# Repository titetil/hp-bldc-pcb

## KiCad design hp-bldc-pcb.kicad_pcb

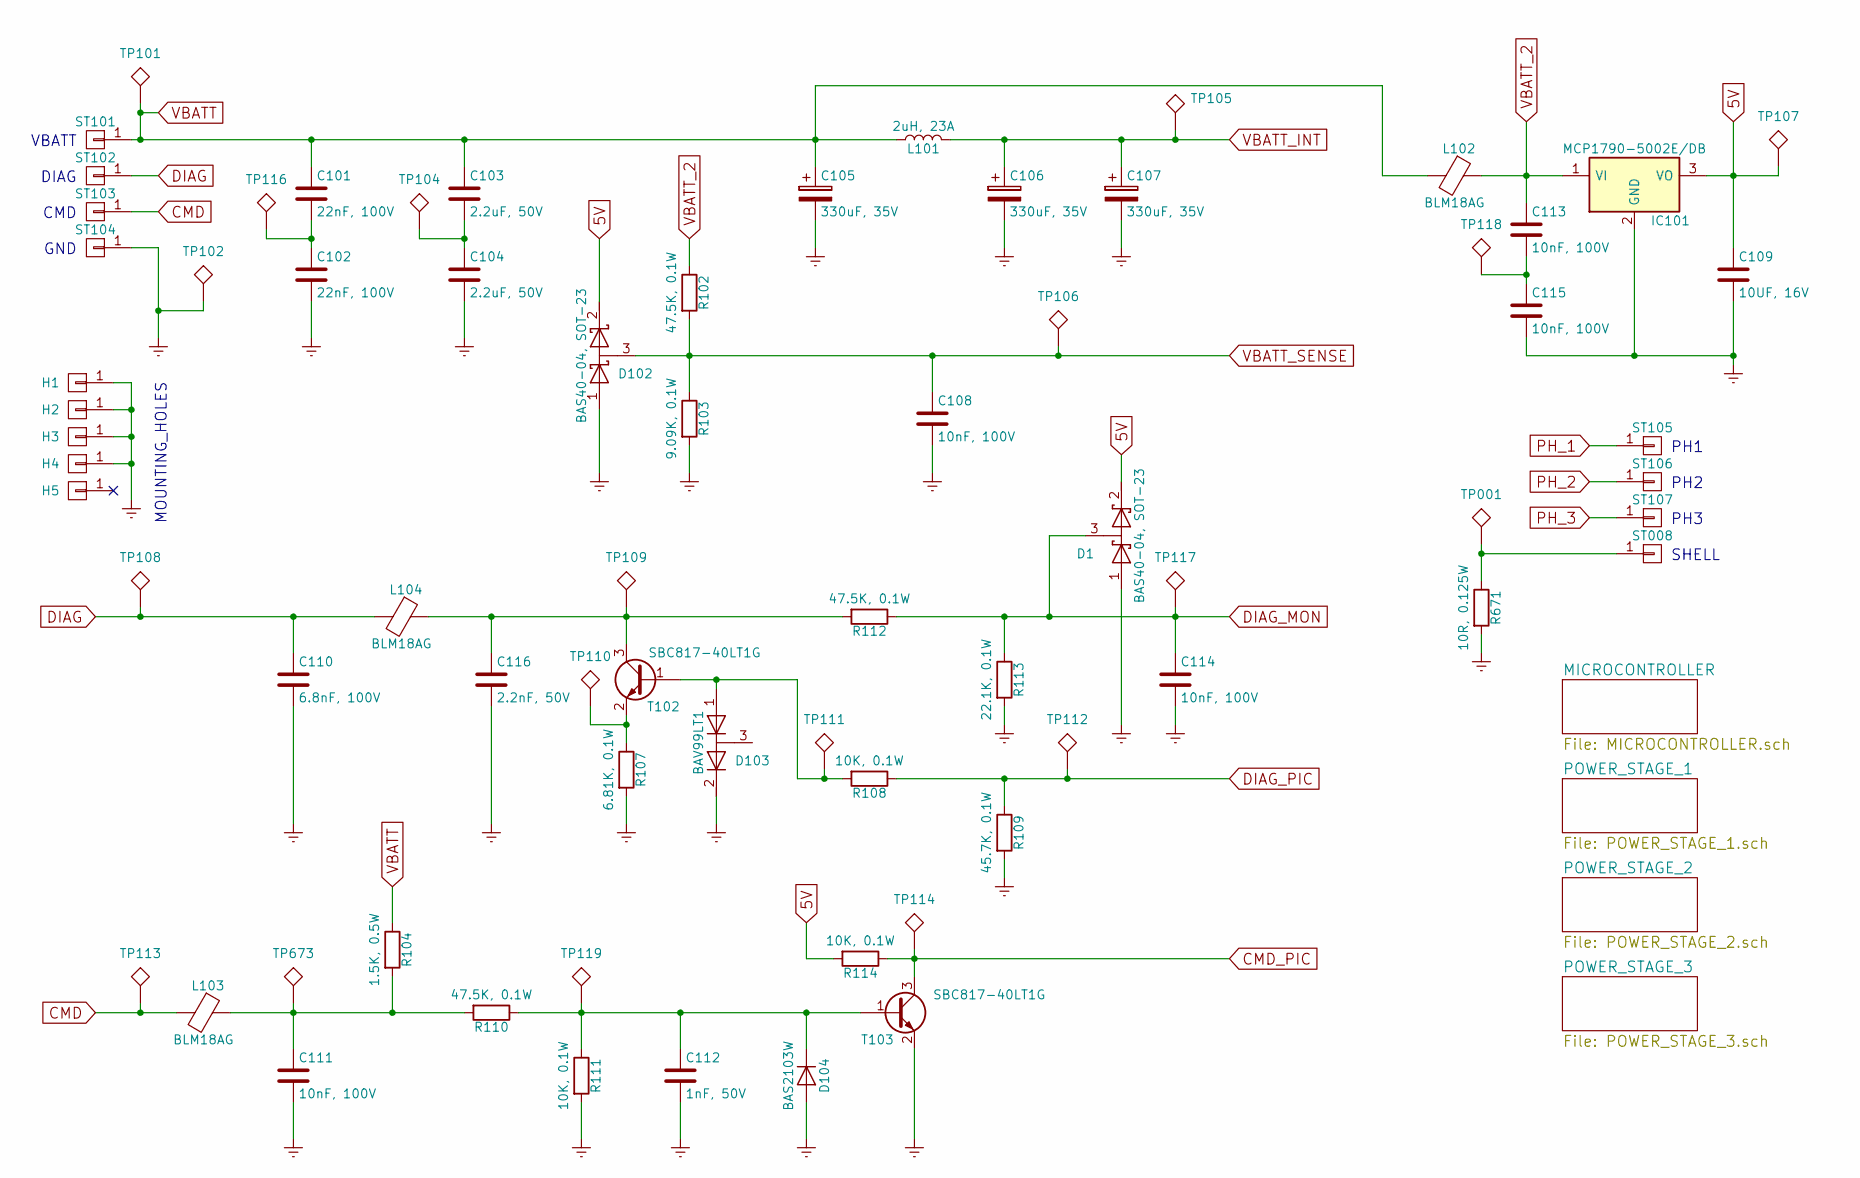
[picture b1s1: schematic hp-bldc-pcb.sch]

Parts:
C101, C102: 22nF, 100V; C_0805
C103, C104: 2.2uF, 50V; C_1206
C105, C106, C107: 330uF, 35V; CP_Elec_10x10
C108, C113, C114, C115: 10nF, 100V; C_0603
C109: 10UF, 16V; C_1206
C110: 6.8nF, 100V; C_0805
C111: 10nF, 100V; C_0805
C112: 1nF, 50V; C_0603
C116: 2.2nF, 50V; C_0603
D1, D102: BAS40-04, SOT-23; SOT-23
D103: BAV99LT1; SOT-23
D104: BAS2103W; D_SOD-323
H1, H2, H3, H4, H5: CONN_01X01; ENCLOSURE_MOUNTING_HOLE
IC101: MCP1790-5002E/DB; SOT-223
L101: 2uH, 23A; L_Wuerth_HCI-1365
L102, L103, L104: BLM18AG; L_0603
R102, R110, R112: 47.5K, 0.1W; R_0603
R103: 9.09K, 0.1W; R_0603
R104: 1.5K, 0.5W; R_1210
R107: 6.81K, 0.1W; R_0603
R108, R111, R114: 10K, 0.1W; R_0603
R109: 45.7K, 0.1W; R_0603
R113: 22.1K, 0.1W; R_0603
R671: 10R, 0.125W; R_0805
ST008, ST101, ST102, ST103, ST104, ST105, ST106, ST107: CONN_01X01; BIG_RECT_PAD
T102, T103: SBC817-40LT1G; SOT-23
TP001, TP101, TP102, TP104, TP105, TP106, TP107, TP108, TP109, TP110, TP111, TP112, TP113, TP114, TP116, TP117, TP118, TP119, TP673: TEST; TEST_POINT_40mil

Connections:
5V: C109.1, D1.2 (K), D102.2 (K), IC101.3 (VO), R114.2, TP107.1; also elsewhere on the board
CMD: L103.2, ST103.1, TP113.1
CMD_PIC: R114.1, T103.3 (C), TP114.1; also elsewhere on the board
DIAG: C110.1, L104.2, ST102.1, TP108.1
DIAG_MON: C114.1, D1.3 (common), R112.1, R113.1, TP117.1; also elsewhere on the board
DIAG_PIC: R108.1, R109.1, TP112.1; also elsewhere on the board
Earth: C102.2, C104.2, C105.2, C106.2, C107.2, C108.2, C109.2, C110.2, C111.2, C112.2, C114.2, C115.2, C116.2, D1.1 (A), D102.1 (A), D103.2 (K), D104.2 (A), H1.1, H2.1, H3.1, H4.1, IC101.2 (GND), IC101.4 (GND), R103.2, R107.2, R109.2, R111.2, R113.2, R671.2, ST104.1, T103.2 (E), TP102.1; also elsewhere on the board
unnamed: C101.2, C102.1, TP116.1
unnamed: C103.2, C104.1, TP104.1
unnamed: C111.1, L103.1, R104.2, R110.2, TP673.1
unnamed: C112.1, D104.1 (K), R110.1, R111.1, T103.1 (B), TP119.1
unnamed: C113.2, C115.1, TP118.1
unnamed: C116.1, L104.1, R112.2, T102.3 (C), TP109.1
unnamed: D103.1 (A), R108.2, T102.1 (B), TP111.1
unnamed: R107.1, T102.2 (E), TP110.1
unnamed: R671.1, ST008.1, TP001.1
PH_1: ST105.1; also elsewhere on the board
PH_2: ST106.1; also elsewhere on the board
PH_3: ST107.1; also elsewhere on the board
VBATT: C101.1, C103.1, C105.1, L101.1, L102.2, R104.1, ST101.1, TP101.1
VBATT_2: C113.1, IC101.1 (VI), L102.1, R102.1
VBATT_INT: C106.1, C107.1, L101.2, TP105.1; also elsewhere on the board
VBATT_SENSE: C108.1, D102.3 (common), R102.2, R103.1, TP106.1; also elsewhere on the board

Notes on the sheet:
PH1
PH2
PH3
SHELL
VBATT
DIAG
CMD
GND
MOUNTING_HOLES

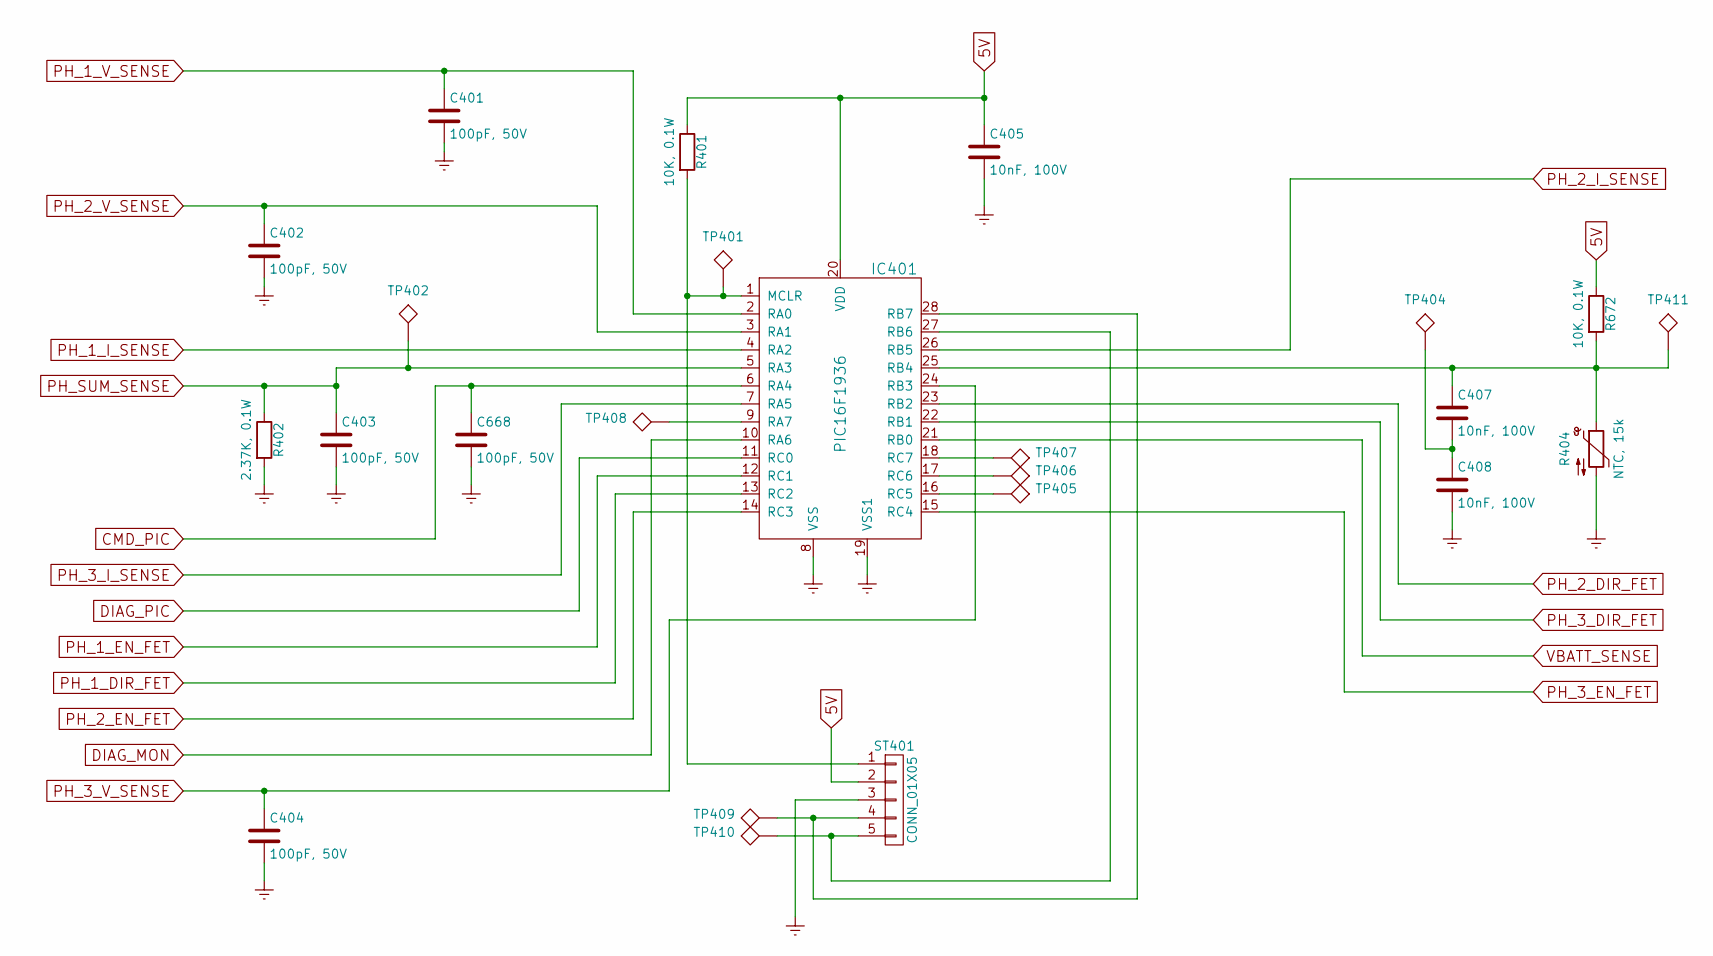
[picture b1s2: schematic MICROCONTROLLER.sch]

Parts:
C401, C402, C403, C404, C668: 100pF, 50V; C_0603
C405, C407, C408: 10nF, 100V; C_0603
IC401: PIC16F1936; SSOP-28_5.3x10.2mm_Pitch0.65mm
R401, R672: 10K, 0.1W; R_0603
R402: 2.37K, 0.1W; R_0603
R404: NTC, 15k; R_0603
ST401: CONN_01X05; Pin_Header_Straight_1x05_Pitch2.54mm_SMD_Pin1Left
TP401, TP402, TP404, TP405, TP406, TP407, TP408, TP409, TP410, TP411: TEST; TEST_POINT_40mil

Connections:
5V: C405.1, IC401.20 (VDD), R401.1, R672.1, ST401.2; also elsewhere on the board
CMD_PIC: C668.1, IC401.6 (RA4); also elsewhere on the board
DIAG_MON: IC401.10 (RA6); also elsewhere on the board
DIAG_PIC: IC401.11 (RC0); also elsewhere on the board
Earth: C401.2, C402.2, C403.2, C404.2, C405.2, C408.2, C668.2, IC401.8 (VSS), IC401.19 (VSS1), R402.2, R404.2, ST401.3; also elsewhere on the board
unnamed: C407.1, IC401.25 (RB4), R404.1, R672.2, TP411.1
unnamed: C407.2, C408.1, TP404.1
unnamed: IC401.1 (MCLR), R401.2, ST401.1, TP401.1
unnamed: IC401.9 (RA7), TP408.1
unnamed: IC401.16 (RC5), TP405.1
unnamed: IC401.17 (RC6), TP406.1
unnamed: IC401.18 (RC7), TP407.1
unnamed: IC401.27 (RB6), ST401.5, TP410.1
unnamed: IC401.28 (RB7), ST401.4, TP409.1
PH_1_DIR_FET: IC401.13 (RC2); also elsewhere on the board
PH_1_EN_FET: IC401.12 (RC1); also elsewhere on the board
PH_1_I_SENSE: IC401.4 (RA2); also elsewhere on the board
PH_1_V_SENSE: C401.1, IC401.2 (RA0); also elsewhere on the board
PH_2_DIR_FET: IC401.23 (RB2); also elsewhere on the board
PH_2_EN_FET: IC401.14 (RC3); also elsewhere on the board
PH_2_I_SENSE: IC401.26 (RB5); also elsewhere on the board
PH_2_V_SENSE: C402.1, IC401.3 (RA1); also elsewhere on the board
PH_3_DIR_FET: IC401.22 (RB1); also elsewhere on the board
PH_3_EN_FET: IC401.15 (RC4); also elsewhere on the board
PH_3_I_SENSE: IC401.7 (RA5); also elsewhere on the board
PH_3_V_SENSE: C404.1, IC401.24 (RB3); also elsewhere on the board
PH_SUM_SENSE: C403.1, IC401.5 (RA3), R402.1, TP402.1; also elsewhere on the board
VBATT_SENSE: IC401.21 (RB0); also elsewhere on the board

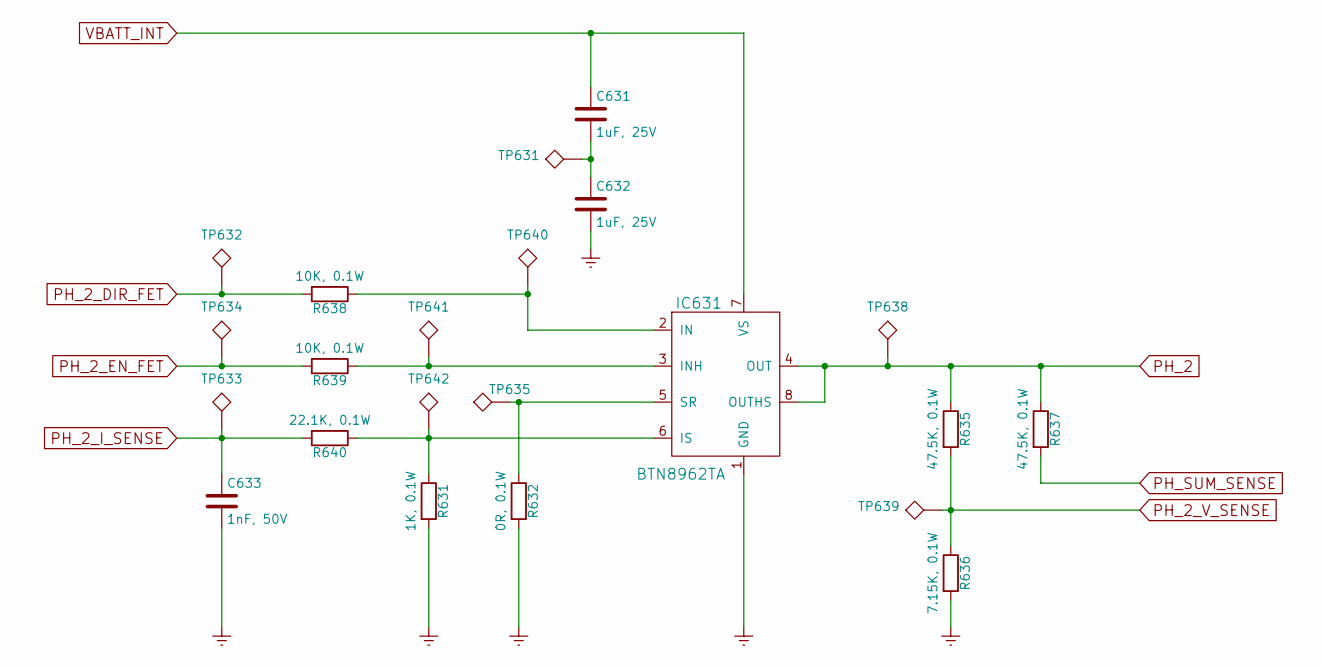
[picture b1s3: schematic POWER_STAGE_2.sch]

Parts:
C631, C632: 1uF, 25V; C_0805
C633: 1nF, 50V; C_0603
IC631: BTN8962TA; TO-263-7_TabPin8
R631: 1K, 0.1W; R_0603
R632: 0R, 0.1W; R_0603
R635, R637: 47.5K, 0.1W; R_0603
R636: 7.15K, 0.1W; R_0603
R638, R639: 10K, 0.1W; R_0603
R640: 22.1K, 0.1W; R_0603
TP631, TP632, TP633, TP634, TP635, TP638, TP639, TP640, TP641, TP642: TEST; TEST_POINT_40mil

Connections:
Earth: C632.2, C633.2, IC631.1 (GND), R631.2, R632.2, R636.2; also elsewhere on the board
unnamed: C631.2, C632.1, TP631.1
unnamed: IC631.2 (IN), R638.1, TP640.1
unnamed: IC631.3 (INH), R639.1, TP641.1
unnamed: IC631.5 (SR), R632.1, TP635.1
unnamed: IC631.6 (IS), R631.1, R640.1, TP642.1
PH_2: IC631.4 (OUT), IC631.8 (OUTHS), R635.1, R637.1, TP638.1; also elsewhere on the board
PH_2_DIR_FET: R638.2, TP632.1; also elsewhere on the board
PH_2_EN_FET: R639.2, TP634.1; also elsewhere on the board
PH_2_I_SENSE: C633.1, R640.2, TP633.1; also elsewhere on the board
PH_2_V_SENSE: R635.2, R636.1, TP639.1; also elsewhere on the board
PH_SUM_SENSE: R637.2; also elsewhere on the board
VBATT_INT: C631.1, IC631.7 (VS); also elsewhere on the board

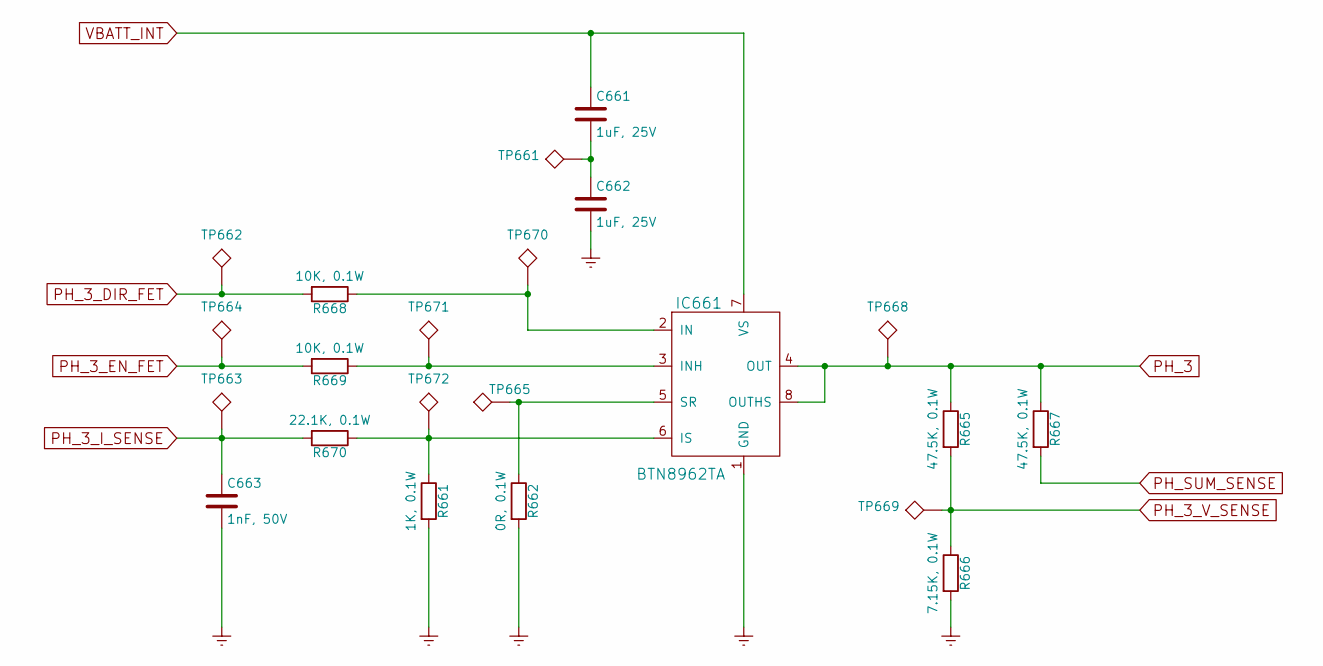
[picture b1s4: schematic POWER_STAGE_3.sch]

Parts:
C661, C662: 1uF, 25V; C_0805
C663: 1nF, 50V; C_0603
IC661: BTN8962TA; TO-263-7_TabPin8
R661: 1K, 0.1W; R_0603
R662: 0R, 0.1W; R_0603
R665, R667: 47.5K, 0.1W; R_0603
R666: 7.15K, 0.1W; R_0603
R668, R669: 10K, 0.1W; R_0603
R670: 22.1K, 0.1W; R_0603
TP661, TP662, TP663, TP664, TP665, TP668, TP669, TP670, TP671, TP672: TEST; TEST_POINT_40mil

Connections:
Earth: C662.2, C663.2, IC661.1 (GND), R661.2, R662.2, R666.2; also elsewhere on the board
unnamed: C661.2, C662.1, TP661.1
unnamed: IC661.2 (IN), R668.1, TP670.1
unnamed: IC661.3 (INH), R669.1, TP671.1
unnamed: IC661.5 (SR), R662.1, TP665.1
unnamed: IC661.6 (IS), R661.1, R670.1, TP672.1
PH_3: IC661.4 (OUT), IC661.8 (OUTHS), R665.1, R667.1, TP668.1; also elsewhere on the board
PH_3_DIR_FET: R668.2, TP662.1; also elsewhere on the board
PH_3_EN_FET: R669.2, TP664.1; also elsewhere on the board
PH_3_I_SENSE: C663.1, R670.2, TP663.1; also elsewhere on the board
PH_3_V_SENSE: R665.2, R666.1, TP669.1; also elsewhere on the board
PH_SUM_SENSE: R667.2; also elsewhere on the board
VBATT_INT: C661.1, IC661.7 (VS); also elsewhere on the board

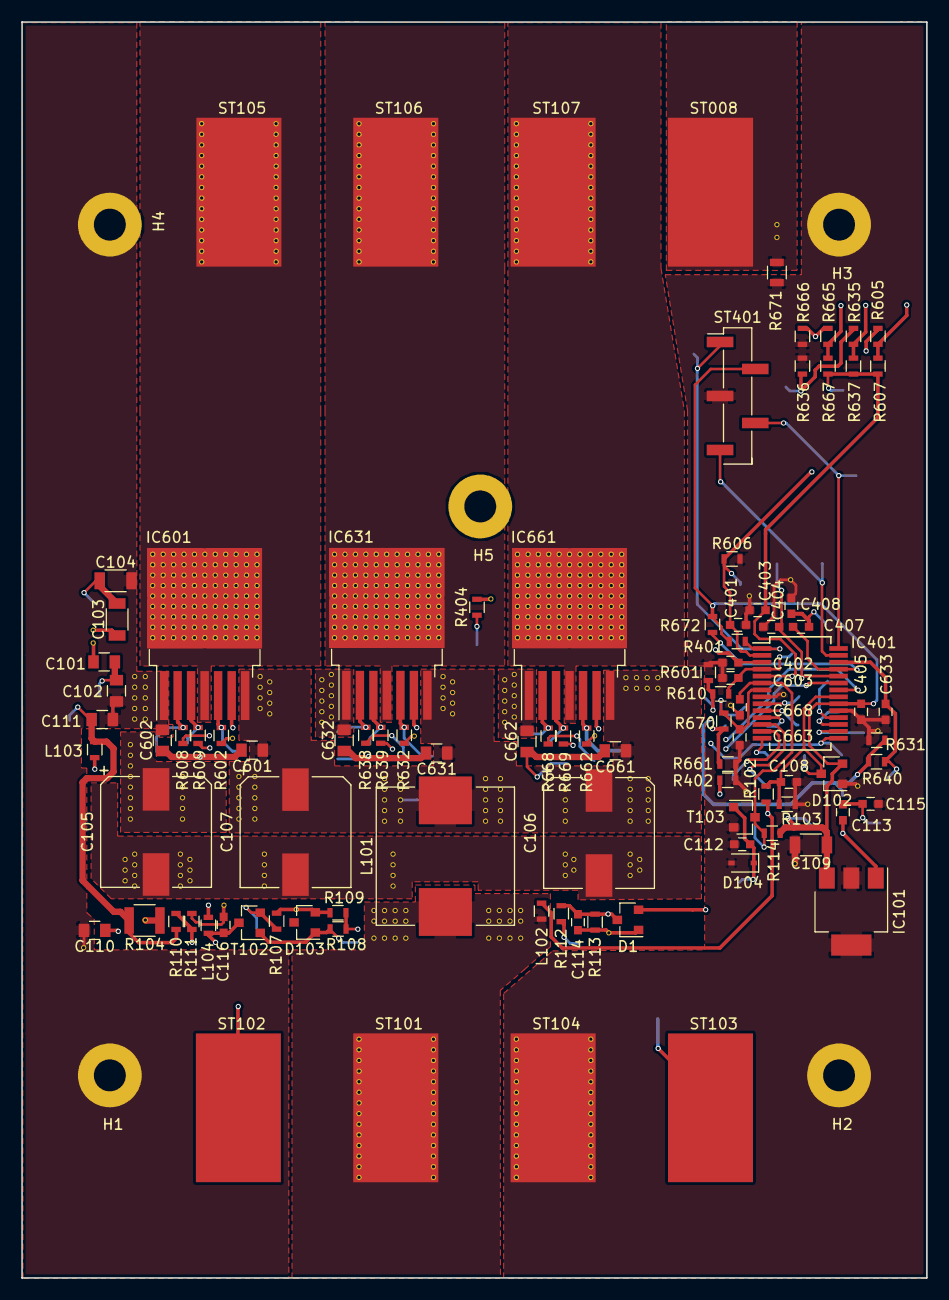
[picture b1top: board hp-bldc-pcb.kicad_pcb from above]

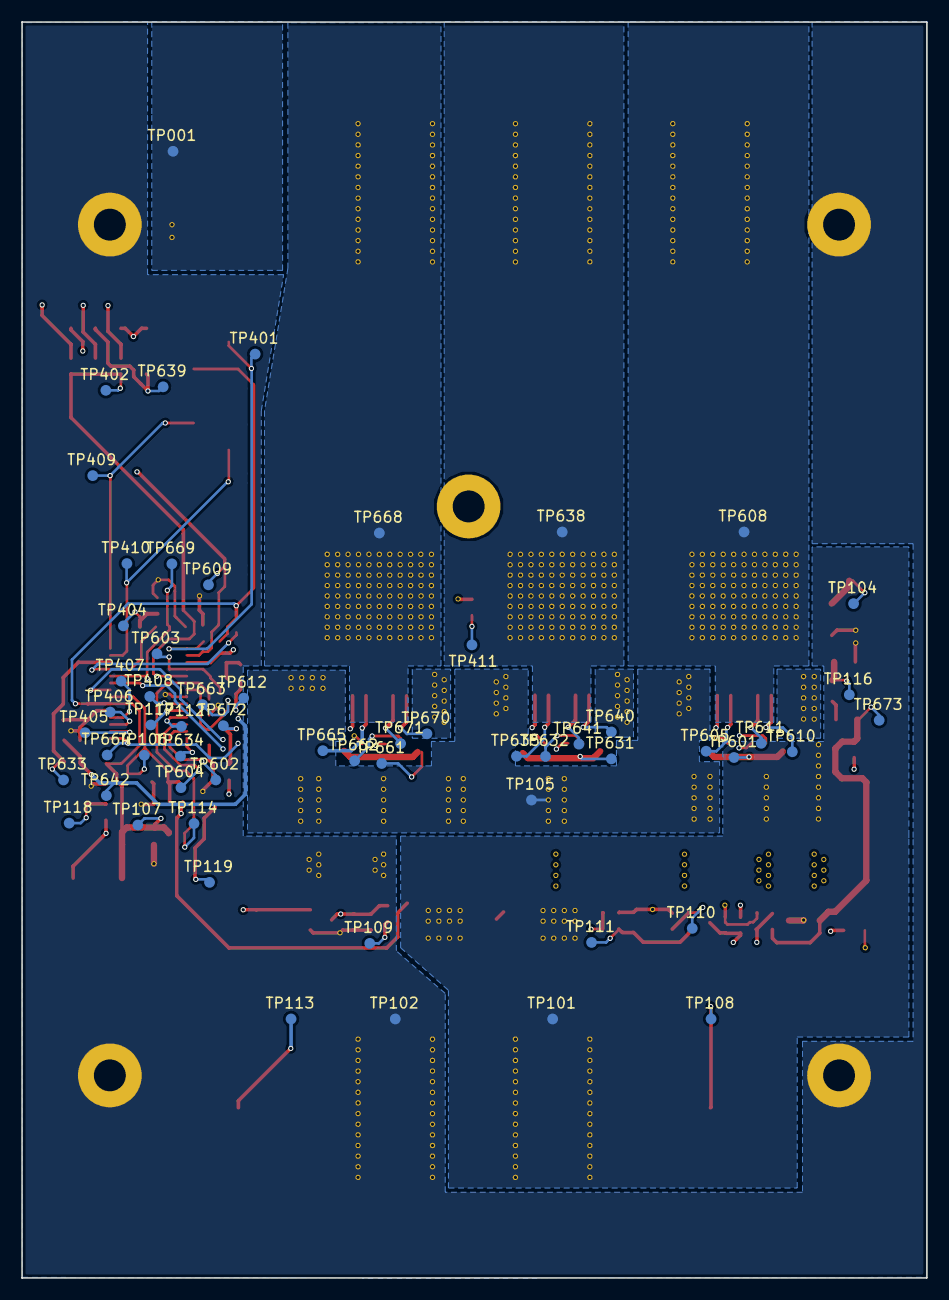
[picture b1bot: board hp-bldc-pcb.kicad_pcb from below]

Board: 4 copper layers, 85.1 x 118.1 mm, 161 parts (59 on the bottom side), 60 nets.

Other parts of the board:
C601, C602: 1uF, 25V; C_0805
C603: 1nF, 50V; C_0603
IC601: BTN8962TA; TO-263-7_TabPin8
R601: 1K, 0.1W; R_0603
R602: 0R, 0.1W; R_0603
R605, R607: 47.5K, 0.1W; R_0603
R606: 7.15K, 0.1W; R_0603
R608, R609: 10K, 0.1W; R_0603
R610: 22.1K, 0.1W; R_0603
TP601, TP602, TP603, TP604, TP605, TP608, TP609, TP610, TP611, TP612: TEST; TEST_POINT_40mil

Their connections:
Earth: C602.2, C603.2, IC601.1, R601.2, R602.2, R606.2; also elsewhere on the board
unnamed: C601.2, C602.1, TP601.1
unnamed: IC601.2, R608.1, TP610.1
unnamed: IC601.3, R609.1, TP611.1
unnamed: IC601.5, R602.1, TP605.1
unnamed: IC601.6, R601.1, R610.1, TP612.1
PH_1: IC601.4, IC601.8, R605.1, R607.1, TP608.1; also elsewhere on the board
PH_1_DIR_FET: R608.2, TP602.1; also elsewhere on the board
PH_1_EN_FET: R609.2, TP604.1; also elsewhere on the board
PH_1_I_SENSE: C603.1, R610.2, TP603.1; also elsewhere on the board
PH_1_V_SENSE: R605.2, R606.1, TP609.1; also elsewhere on the board
PH_SUM_SENSE: R607.2; also elsewhere on the board
VBATT_INT: C601.1, IC601.7; also elsewhere on the board

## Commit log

2018-02-06 - Initial commit.
2018-02-14 - Finished traces. Now copper areas.
2018-02-15 - Finished putting down copper areas.
2018-02-15 - Almost done with PCB. Need to fix a few errors.
2018-02-16 - Finished v1.0
2018-03-22 - Finished adaptation to JMS board footprint. - Added testpoints. - Changed header connector to 0.1" pitch, and tall.
2018-06-19 - Minor changes to silkscreen. - Minor changes to BOM. - Additions to Readme file. - Page layout changed in schematic.
2018-09-24 -Changed naming convention of gerber zip file.
2018-10-08 - Added TP411 at JMS request. This was needed to test the NTC during ICT.
